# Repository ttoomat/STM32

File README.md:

Всем привет, здесь мои проекты по STM32. Для каждого я написала небольшой README. Некоторые из проектов связаны с курсом по микроконтроллерам в ИТМО. Более полноценные проекты буду делать отдельными репозиториями.

Напоминание: для сохранения русского README.md в Far Manager и отображения в гитхабе - кодировка UTF-8 (Shift+F8 смена кодировки).

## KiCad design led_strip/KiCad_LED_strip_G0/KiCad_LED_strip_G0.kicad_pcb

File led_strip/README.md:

# Светодиодная лента

Просто ШИМ на таймере (для белого цвета), работает при DATA 3.3В, push-pull. Подождать пока запишутся данные и нажать RESET на МК. Можно отключить МК после записи всех данных. Но память светодиодов энергозависимая.

Выход: переделать на STM32G030!

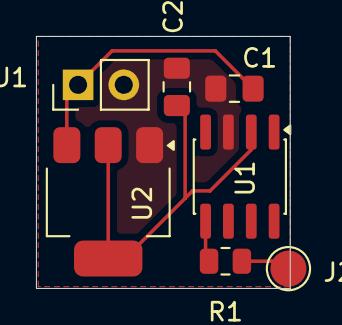
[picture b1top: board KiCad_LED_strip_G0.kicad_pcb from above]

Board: 2 copper layers, 14.1 x 14.0 mm, 7 parts (0 on the bottom side), 5 nets.

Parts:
C1: 10u; C_0805_2012Metric_Pad1.18x1.45mm_HandSolder
C2: 22u; C_0805_2012Metric_Pad1.18x1.45mm_HandSolder
J1: 5V; PinHeader_1x02_P2.54mm_Vertical
J2: Conn_01x01; TestPoint_Pad_D2.0mm
R1: 150; R_0805_2012Metric
U1: STM32G030J6Mx; SOIC-8_3.9x4.9mm_P1.27mm
U2: AMS1117-3.3; SOT-223-3_TabPin2

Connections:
5V: C1.1, J1.1, U2.3 (VI)
+3V3: C2.1, U1.2 (VDD), U2.2 (VO)
GND: C1.2, C2.2, J1.2, U1.3 (VSS), U2.1 (GND)
LED_DATA: J2.1 (Pin_1_1), R1.1
unnamed: R1.2, U1.5 (PA8/PA9/PA11/PB0/PB1)

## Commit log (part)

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2025-03-13 Setup snake.
    Half-empty functions with correct logic. TODO: timer, function realizations, apple render, buttons.
2025-03-13 Move function & directions enum.
2025-03-13 Button interuptions.
    Also added: if you were moving left, you can't move right without moving up/down first.
2025-03-13 Eating apple.
    Todo: intersection & better timer.
2025-03-14 Intersection with the tail added.
    TODO: timer, readme.
2025-03-14 Schematics added.
2025-03-14 Add resistors to the schematic.
2025-03-14 Snake: working version.
2025-03-14 Snake photos added.
2025-03-14 Create README.md
    For Snake
2025-03-17 Advanced way to turn on a led.
    GPIOC->ODR |= (1 << 3);
    instead of:
    HAL_GPIO_WritePin(GPIOC, GPIO_PIN_3, GPIO_PIN_SET);
2025-03-17 Uart transmit start.
    Connect with putty, Serial, 9600 baudrate.
2025-03-17 UART receeive & transmit.
    That's holy magic.
2025-03-18 Uart with interruptions.
2025-03-18 4 digit segment display add.
2025-03-18 Display sequence change.
2025-03-18 Stopwatch (under 2 mins).
    Todo: check why after 2 minutes goes 0 again. Too small type used?
2025-03-18 Stopwatch (mm:ss).
2025-03-19 Lab 2: commands added.
    Todo: DATA command.
2025-03-19 Lab2 commands done.
    Difference from the task: only 2 leds.
2025-03-19 Drawing sinus project start.
    ITMO University MCU course lab 3.
2025-03-20 Sin: working Uart.
    Interruptions enabled.
2025-03-31 Float number UART transmit.
    enable using floats: Properties > C/C++ Build > Settings > MCU Settings > Use float in scanf, printf
2025-03-31 Sin in console.
    Idk why timer is 0, 2, 4, 6, ...
2025-03-31 Sinus on oscillator.
    Incorrect time in console, but who cares.
    Lab 3 done.
2025-07-15 Readme added.
    Few words for every project.
2025-07-15 Update README.md
    typo
2025-07-15 Servo rotates somehow.
    sConfigOC.Pulse = 1; or 2 makes rotation.
2025-07-18 PWM 2ms/20ms.
    We got rectangular wave with period 20ms and width 2ms. Here you can check Prescaler etc.
2025-07-24 New project started.
2025-08-01 Not working display.
    Maybe I need to change registers...
2025-08-13 Blue pill wink.
    STM32 F103C8T6 board project.
    Before we had NUCLEO STM32 F446RE projects.
    Added firmware into user/STM32Cube/Repository
2025-09-01 LCD Bluepill project.
    Minimal LCD project. No LCD libs. Custom character <3
